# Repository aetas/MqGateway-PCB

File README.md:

# MqGateway PCB projects

Schematics and PCB design for MqGateway boards.

Source files can be read with [KiCad](https://kicad-pcb.org/). GERBER files are available in the [releases](https://github.com/aetas/MqGateway-PCB/releases).

Read more about MqGateway on the [documentation site](https://mqgateway.com).

## Issues

If you have found any problem with the PCB projects - please create an issue in [aetas/mqgateway repository](https://github.com/aetas/mqgateway).

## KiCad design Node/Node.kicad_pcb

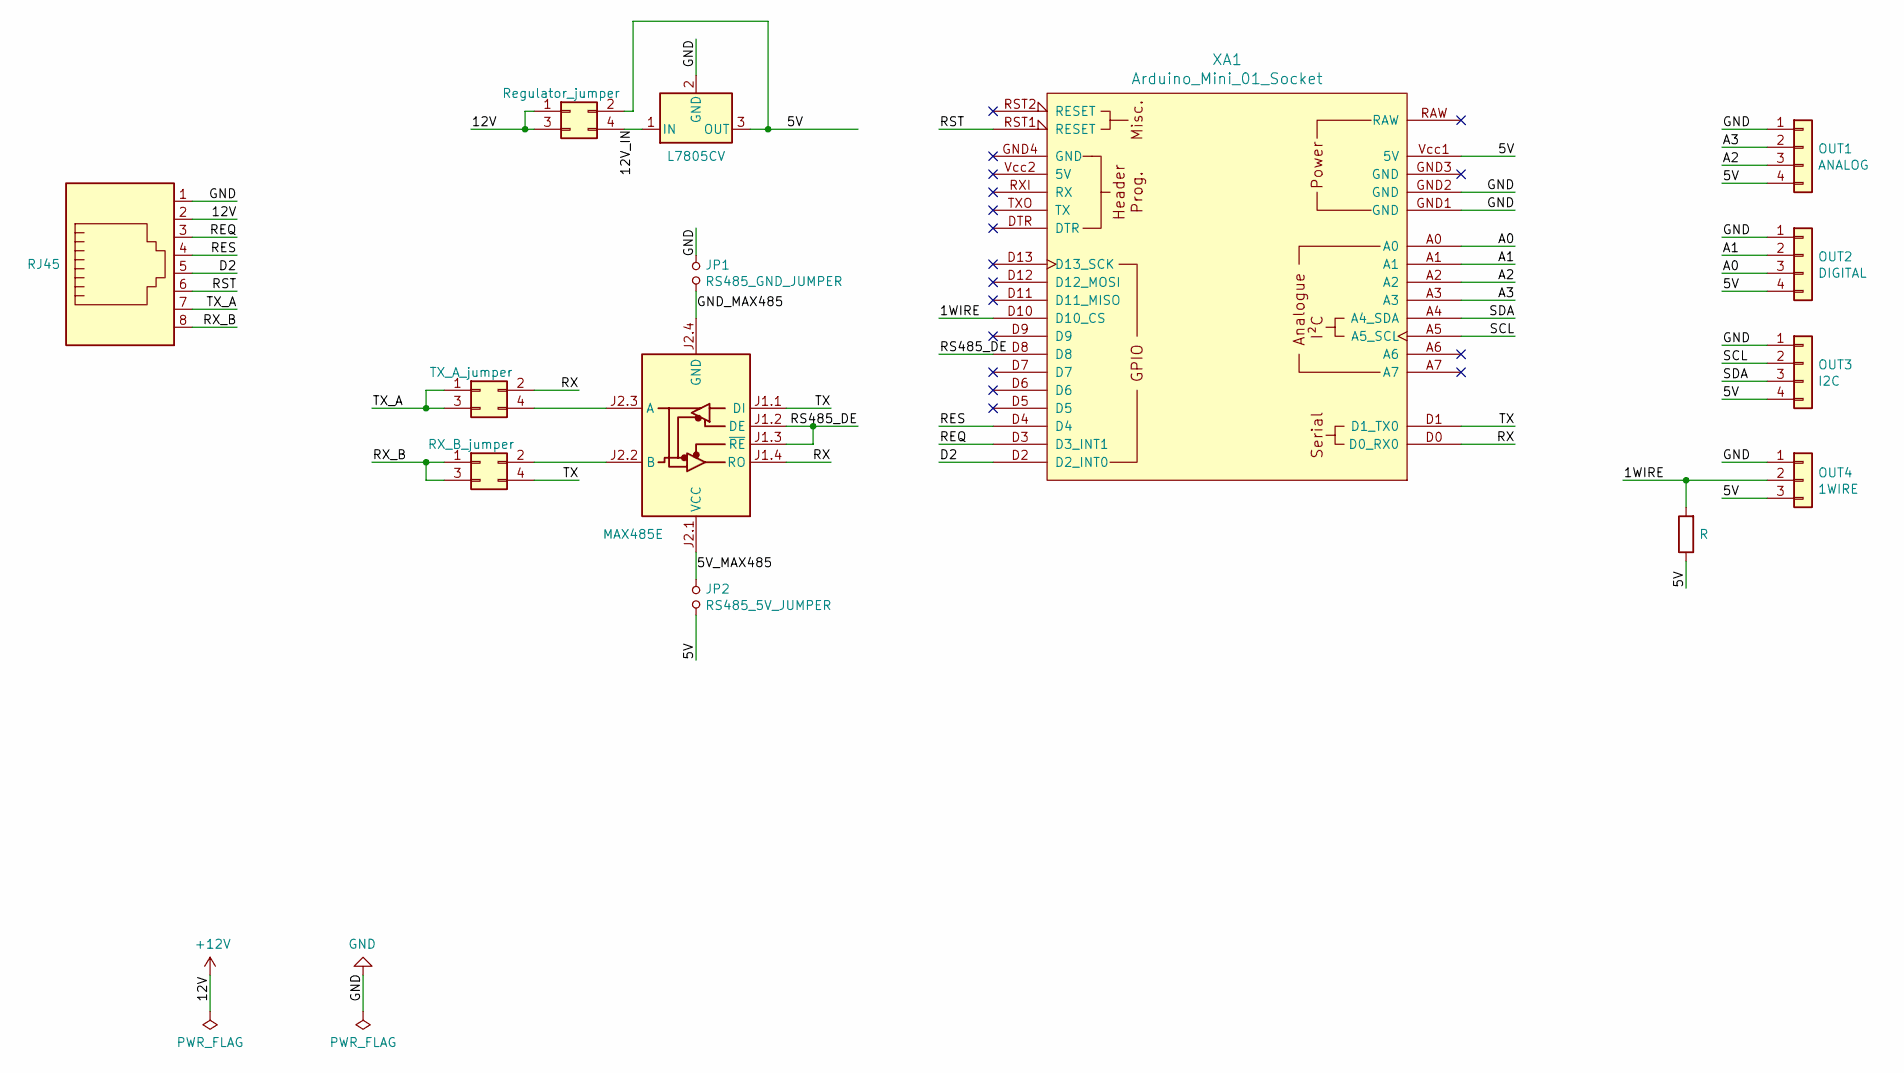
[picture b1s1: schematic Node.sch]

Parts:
J1: Regulator_jumper; pin_strip_2x2
J2: RX_B_jumper; pin_strip_2x2
J3: TX_A_jumper; pin_strip_2x2
J4: RJ45; RJ45_Amphenol_54602-x08_Horizontal
JP1: RS485_GND_JUMPER; pin_strip_2
JP2: RS485_5V_JUMPER; pin_strip_2
OUT1: ANALOG; Molex_PicoBlade_53047-0410_1x04_P1.25mm_Vertical
OUT2: DIGITAL; Molex_PicoBlade_53047-0410_1x04_P1.25mm_Vertical
OUT3: I2C; Molex_PicoBlade_53047-0410_1x04_P1.25mm_Vertical
OUT4: 1WIRE; Molex_PicoBlade_53047-0310_1x03_P1.25mm_Vertical
R1: R; R_Axial_DIN0204_L3.6mm_D1.6mm_P7.62mm_Horizontal
U1: MAX485E; RS485-TTL-CONVERTER
U2: L7805CV; TO-220-3_Vertical
XA1: Arduino_Mini_01_Socket; Arduino_Pro_Mini_Clone_Socket

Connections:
+12V: J1.1, J1.3, J4.2
/1WIRE: OUT4.2, R1.2, XA1.D10 (D10_CS)
/5V: J1.2, JP2.1, OUT1.4, OUT2.4, OUT3.4, OUT4.3, R1.1, U2.3 (OUT), XA1.Vcc1 (5V)
/5V_MAX485: JP2.2, U1.J2.1 (VCC)
/12V_IN: J1.4, U2.1 (IN)
/A0: OUT2.3, XA1.A0
/A1: OUT2.2, XA1.A1
/A2: OUT1.3, XA1.A2
/A3: OUT1.2, XA1.A3
/D2: J4.5, XA1.D2 (D2_INT0)
/GND_MAX485: JP1.1, U1.J2.4 (GND)
/REQ: J4.3, XA1.D3 (D3_INT1)
/RES: J4.4, XA1.D4
/RS485_DE: U1.J1.2 (DE), U1.J1.3 (~RE), XA1.D8
/RST: J4.6, XA1.RST1 (RESET)
/RX: J3.2, U1.J1.4 (RO), XA1.D0 (D0_RX0)
/RX_B: J2.1, J2.3, J4.8
/SCL: OUT3.2, XA1.A5 (A5_SCL)
/SDA: OUT3.3, XA1.A4 (A4_SDA)
/TX: J2.4, U1.J1.1 (DI), XA1.D1 (D1_TX0)
/TX_A: J3.1, J3.3, J4.7
GND: J4.1, JP1.2, OUT1.1, OUT2.1, OUT3.1, OUT4.1, U2.2 (GND), XA1.GND1 (GND), XA1.GND2 (GND)
unnamed: J2.2, U1.J2.2 (B)
unnamed: J3.4, U1.J2.3 (A)

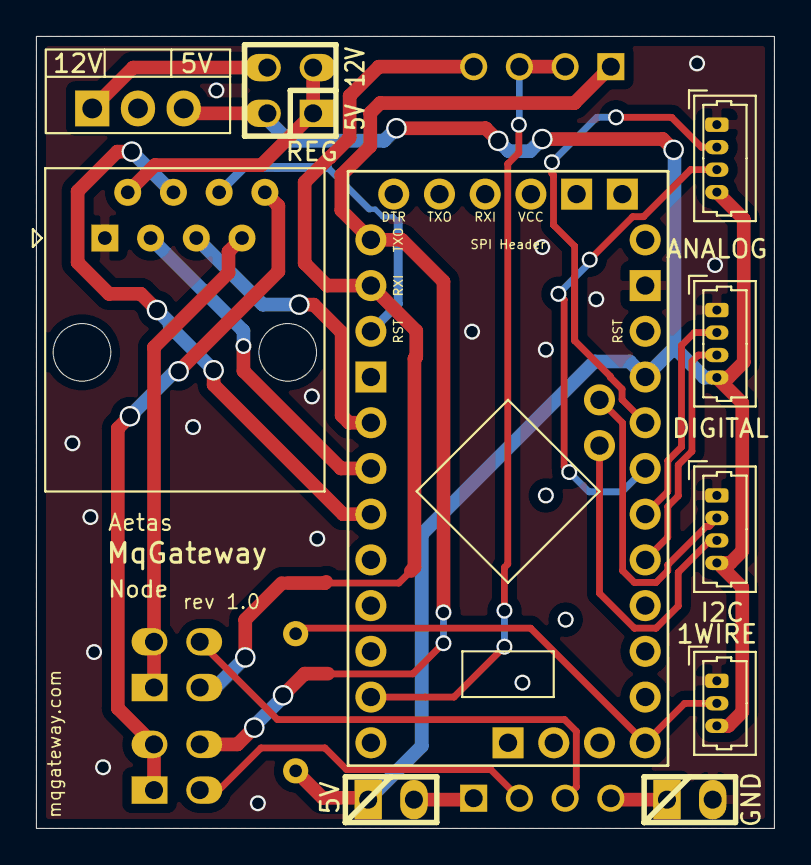
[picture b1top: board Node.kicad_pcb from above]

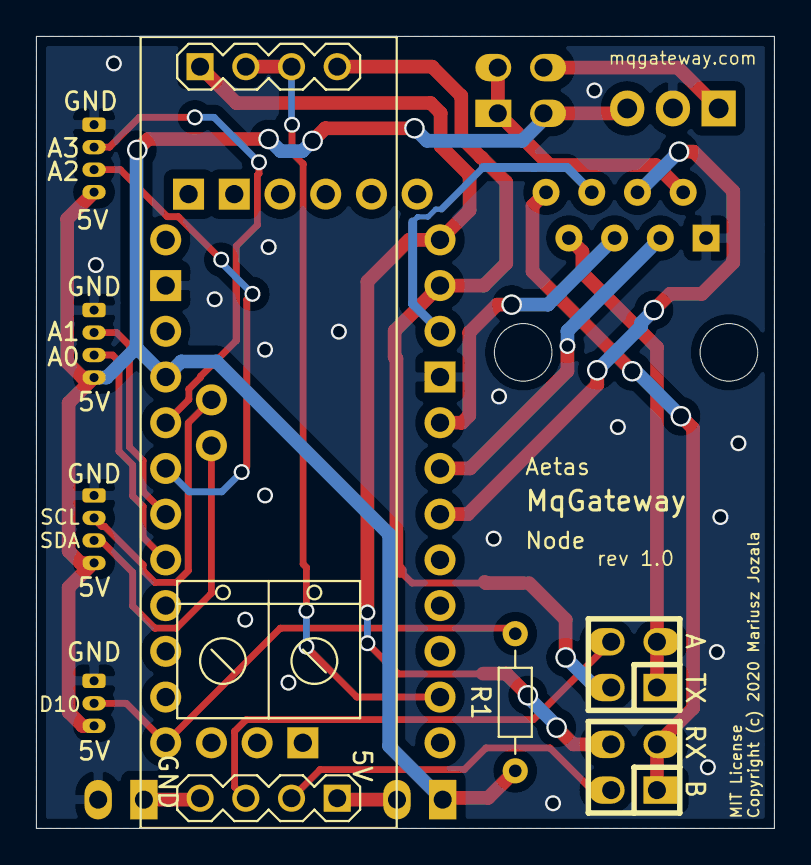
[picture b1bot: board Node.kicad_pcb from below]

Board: 2 copper layers, 41.0 x 44.0 mm, 14 parts (4 on the bottom side), 24 nets.

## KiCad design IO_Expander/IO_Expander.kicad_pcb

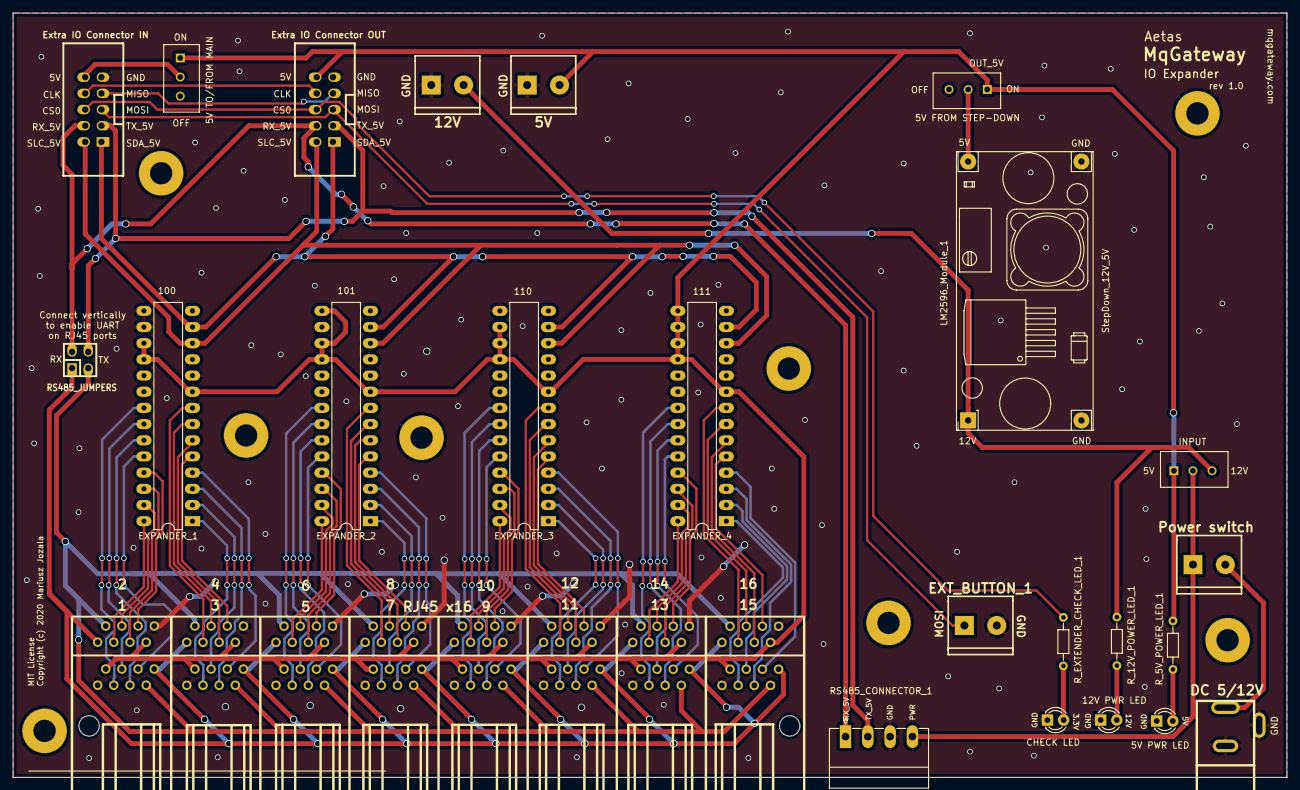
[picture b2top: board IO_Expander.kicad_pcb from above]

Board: 2 copper layers, 200.0 x 120.0 mm, 24 parts (0 on the bottom side), 84 nets.

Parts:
5V_OUTPUT_1: 5V; mors_2p
5V_POWER_LED_1: 5V PWR LED; LED_D3.0mm
12V_OUTPUT_1: 12V; mors_2p
12V_POWER_LED_1: 12V PWR LED; LED_D3.0mm
DC_JACK_1: DC 5/12V; dc_socket
EXPANDER_1, EXPANDER_2, EXPANDER_3, EXPANDER_4: MCP23017_SP; DIP-28_W7.62mm_LongPads
EXTENDER_CHECK_LED_1: CHECK LED; LED_D3.0mm
EXTRA_IO_CONNECTOR_1: Extra IO Connector IN; vasch_strip_5x2
EXTRA_IO_CONNECTOR_2: Extra IO Connector OUT; vasch_strip_5x2
EXT_BUTTON_1: Screw_Terminal_01x02; mors_2p
LM2596_Module_1: StepDown_12V_5V; YAAJ_DCDC_StepDown_LM2596
POWER_SWITCH_1: Power switch; mors_2p
RJ45x16_1: RJ45 x16; 8p8c_2x8_roomhub
RS485_CONNECTOR_1: RS485 Connector; PhoenixContact_MC-G_04x3.50mm_Angled
RS485_OUT_Jumpers_1: RS485_JUMPERS; pin_strip_2x2
R_5V_POWER_LED_1, R_12V_POWER_LED_1: R_POWER_LED; R_Axial_DIN0204_L3.6mm_D1.6mm_P7.62mm_Horizontal
R_EXTENDER_CHECK_LED_1: R_EXTENDER_CHECK_LED; R_Axial_DIN0204_L3.6mm_D1.6mm_P7.62mm_Horizontal
SW_SLIDE_SPDT_1: SW_EXTRA_5V_ONOFF; SW_SPDT-3mm
SW_SLIDE_SPDT_2: SW_5V_OR_12V; SW_SPDT-3mm
SW_SLIDE_SPDT_3: 5V FROM STEP-DOWN; SW_SPDT-3mm

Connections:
+5V: 5V_OUTPUT_1.2, EXPANDER_1.9, EXPANDER_1.17, EXPANDER_1.18, EXPANDER_2.9, EXPANDER_2.15, EXPANDER_2.17, EXPANDER_2.18, EXPANDER_3.9, EXPANDER_3.16, EXPANDER_3.17, EXPANDER_3.18, EXPANDER_4.9, EXPANDER_4.15, EXPANDER_4.16, EXPANDER_4.17, EXPANDER_4.18, EXTRA_IO_CONNECTOR_2.10, RJ45x16_1.1.2, RJ45x16_1.2.2, RJ45x16_1.3.2, RJ45x16_1.4.2, RJ45x16_1.5.2, RJ45x16_1.6.2, RJ45x16_1.7.2, RJ45x16_1.8.2, RJ45x16_1.9.2, RJ45x16_1.10.2, RJ45x16_1.11.2, RJ45x16_1.12.2, RJ45x16_1.13.2, RJ45x16_1.14.2, RJ45x16_1.15.2, RJ45x16_1.16.2, R_5V_POWER_LED_1.2, SW_SLIDE_SPDT_1.1, SW_SLIDE_SPDT_2.1, SW_SLIDE_SPDT_3.1
+12V: 12V_OUTPUT_1.2, LM2596_Module_1.1, R_12V_POWER_LED_1.2, SW_SLIDE_SPDT_2.3
/CLK0: EXTRA_IO_CONNECTOR_1.8, EXTRA_IO_CONNECTOR_2.8
/CS0: EXTRA_IO_CONNECTOR_1.6, EXTRA_IO_CONNECTOR_2.6, R_EXTENDER_CHECK_LED_1.2
/MISO0: EXTRA_IO_CONNECTOR_1.7, EXTRA_IO_CONNECTOR_2.7
/MOSI0: EXTRA_IO_CONNECTOR_1.5, EXTRA_IO_CONNECTOR_2.5, EXT_BUTTON_1.1
/POWER: POWER_SWITCH_1.1, RS485_CONNECTOR_1.4, SW_SLIDE_SPDT_2.2
/POWER_START: DC_JACK_1.3, POWER_SWITCH_1.2
/RX1_5V: EXTRA_IO_CONNECTOR_1.4, EXTRA_IO_CONNECTOR_2.4, RS485_CONNECTOR_1.1, RS485_OUT_Jumpers_1.2
/RX1_OUT: RJ45x16_1.1.8, RJ45x16_1.2.8, RJ45x16_1.3.8, RJ45x16_1.4.8, RJ45x16_1.5.8, RJ45x16_1.6.8, RJ45x16_1.7.8, RJ45x16_1.8.8, RJ45x16_1.9.8, RJ45x16_1.10.8, RJ45x16_1.11.8, RJ45x16_1.12.8, RJ45x16_1.13.8, RJ45x16_1.14.8, RJ45x16_1.15.8, RJ45x16_1.16.8, RS485_OUT_Jumpers_1.1
/SCL1_HV: EXPANDER_1.12, EXPANDER_2.12, EXPANDER_3.12, EXPANDER_4.12, EXTRA_IO_CONNECTOR_1.2, EXTRA_IO_CONNECTOR_2.2
/SDA1_HV: EXPANDER_1.13, EXPANDER_2.13, EXPANDER_3.13, EXPANDER_4.13, EXTRA_IO_CONNECTOR_1.1, EXTRA_IO_CONNECTOR_2.1
/TX1_5V: EXTRA_IO_CONNECTOR_1.3, EXTRA_IO_CONNECTOR_2.3, RS485_CONNECTOR_1.2, RS485_OUT_Jumpers_1.4
/TX1_OUT: RJ45x16_1.1.7, RJ45x16_1.2.7, RJ45x16_1.3.7, RJ45x16_1.4.7, RJ45x16_1.5.7, RJ45x16_1.6.7, RJ45x16_1.7.7, RJ45x16_1.8.7, RJ45x16_1.9.7, RJ45x16_1.10.7, RJ45x16_1.11.7, RJ45x16_1.12.7, RJ45x16_1.13.7, RJ45x16_1.14.7, RJ45x16_1.15.7, RJ45x16_1.16.7, RS485_OUT_Jumpers_1.3
GND: 5V_OUTPUT_1.1, 5V_POWER_LED_1.1, 12V_OUTPUT_1.1, 12V_POWER_LED_1.1, DC_JACK_1.1, DC_JACK_1.2, EXPANDER_1.10, EXPANDER_1.15, EXPANDER_1.16, EXPANDER_2.10, EXPANDER_2.16, EXPANDER_3.10, EXPANDER_3.15, EXPANDER_4.10, EXTENDER_CHECK_LED_1.1, EXTRA_IO_CONNECTOR_1.9, EXTRA_IO_CONNECTOR_2.9, EXT_BUTTON_1.2, LM2596_Module_1.2, LM2596_Module_1.3, RJ45x16_1.1.1, RJ45x16_1.2.1, RJ45x16_1.3.1, RJ45x16_1.4.1, RJ45x16_1.5.1, RJ45x16_1.6.1, RJ45x16_1.7.1, RJ45x16_1.8.1, RJ45x16_1.9.1, RJ45x16_1.10.1, RJ45x16_1.11.1, RJ45x16_1.12.1, RJ45x16_1.13.1, RJ45x16_1.14.1, RJ45x16_1.15.1, RJ45x16_1.16.1, RS485_CONNECTOR_1.3
unnamed: 5V_POWER_LED_1.2, R_5V_POWER_LED_1.1
unnamed: 12V_POWER_LED_1.2, R_12V_POWER_LED_1.1
unnamed: EXPANDER_1.1, RJ45x16_1.3.3
unnamed: EXPANDER_1.2, RJ45x16_1.3.4
unnamed: EXPANDER_1.3, RJ45x16_1.3.5
unnamed: EXPANDER_1.4, RJ45x16_1.3.6
unnamed: EXPANDER_1.5, RJ45x16_1.4.3
unnamed: EXPANDER_1.6, RJ45x16_1.4.4
unnamed: EXPANDER_1.7, RJ45x16_1.4.5
unnamed: EXPANDER_1.8, RJ45x16_1.4.6
unnamed: EXPANDER_1.21, RJ45x16_1.1.3
unnamed: EXPANDER_1.22, RJ45x16_1.1.4
unnamed: EXPANDER_1.23, RJ45x16_1.1.5
unnamed: EXPANDER_1.24, RJ45x16_1.1.6
unnamed: EXPANDER_1.25, RJ45x16_1.2.3
unnamed: EXPANDER_1.26, RJ45x16_1.2.4
unnamed: EXPANDER_1.27, RJ45x16_1.2.5
unnamed: EXPANDER_1.28, RJ45x16_1.2.6
unnamed: EXPANDER_2.1, RJ45x16_1.7.3
unnamed: EXPANDER_2.2, RJ45x16_1.7.4
unnamed: EXPANDER_2.3, RJ45x16_1.7.5
unnamed: EXPANDER_2.4, RJ45x16_1.7.6
unnamed: EXPANDER_2.5, RJ45x16_1.8.3
unnamed: EXPANDER_2.6, RJ45x16_1.8.4
unnamed: EXPANDER_2.7, RJ45x16_1.8.5
unnamed: EXPANDER_2.8, RJ45x16_1.8.6
unnamed: EXPANDER_2.21, RJ45x16_1.5.3
unnamed: EXPANDER_2.22, RJ45x16_1.5.4
unnamed: EXPANDER_2.23, RJ45x16_1.5.5
unnamed: EXPANDER_2.24, RJ45x16_1.5.6
unnamed: EXPANDER_2.25, RJ45x16_1.6.3
unnamed: EXPANDER_2.26, RJ45x16_1.6.4
unnamed: EXPANDER_2.27, RJ45x16_1.6.5
unnamed: EXPANDER_2.28, RJ45x16_1.6.6
unnamed: EXPANDER_3.1, RJ45x16_1.11.3
unnamed: EXPANDER_3.2, RJ45x16_1.11.4
unnamed: EXPANDER_3.3, RJ45x16_1.11.5
unnamed: EXPANDER_3.4, RJ45x16_1.11.6
unnamed: EXPANDER_3.5, RJ45x16_1.12.3
unnamed: EXPANDER_3.6, RJ45x16_1.12.4
unnamed: EXPANDER_3.7, RJ45x16_1.12.5
unnamed: EXPANDER_3.8, RJ45x16_1.12.6
unnamed: EXPANDER_3.21, RJ45x16_1.9.3
unnamed: EXPANDER_3.22, RJ45x16_1.9.4
unnamed: EXPANDER_3.23, RJ45x16_1.9.5
unnamed: EXPANDER_3.24, RJ45x16_1.9.6
unnamed: EXPANDER_3.25, RJ45x16_1.10.3
unnamed: EXPANDER_3.26, RJ45x16_1.10.4
unnamed: EXPANDER_3.27, RJ45x16_1.10.5
unnamed: EXPANDER_3.28, RJ45x16_1.10.6
unnamed: EXPANDER_4.1, RJ45x16_1.15.3
unnamed: EXPANDER_4.2, RJ45x16_1.15.4
unnamed: EXPANDER_4.3, RJ45x16_1.15.5
unnamed: EXPANDER_4.4, RJ45x16_1.15.6
unnamed: EXPANDER_4.5, RJ45x16_1.16.3
unnamed: EXPANDER_4.6, RJ45x16_1.16.4
unnamed: EXPANDER_4.7, RJ45x16_1.16.5
unnamed: EXPANDER_4.8, RJ45x16_1.16.6
unnamed: EXPANDER_4.21, RJ45x16_1.13.3
unnamed: EXPANDER_4.22, RJ45x16_1.13.4
unnamed: EXPANDER_4.23, RJ45x16_1.13.5
unnamed: EXPANDER_4.24, RJ45x16_1.13.6
unnamed: EXPANDER_4.25, RJ45x16_1.14.3
unnamed: EXPANDER_4.26, RJ45x16_1.14.4
unnamed: EXPANDER_4.27, RJ45x16_1.14.5
unnamed: EXPANDER_4.28, RJ45x16_1.14.6
unnamed: EXTENDER_CHECK_LED_1.2, R_EXTENDER_CHECK_LED_1.1
unnamed: EXTRA_IO_CONNECTOR_1.10, SW_SLIDE_SPDT_1.2
unnamed: LM2596_Module_1.4, SW_SLIDE_SPDT_3.2

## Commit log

2021-01-16 Publishing boards
2021-04-20 BOM files added for MqGateway mainboard and I/O Expander Board
2022-02-23 Photos and renders of MqGateway boards added
2022-04-18 MqGateway Node v1 added

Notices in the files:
IO_Expander/IO_Expander.kicad_pcb:
MIT License
Copyright (c) 2020 Mariusz Jozala
